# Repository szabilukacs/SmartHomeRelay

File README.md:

# SmartHome Relay 🌡️🔔

This project is a smart boiler control and monitoring system built on the **Blynk platform**. Using an **ESP32**, this system allows users to:  
- **Remotely control a relay** to activate or deactivate the built-in heating resistance of the boiler.  
- **Monitor the temperature** inside the boiler in real-time.  
- **Automate boiler heating** using thermostat-like behavior based on a set temperature range.  
- **Enable or disable notifications** for temperature changes or system events.

The project combines hardware design, embedded programming, and IoT integration for a seamless smart home experience.

---

## 📜 Table of Contents  

- [✨ Features](#features)  
- [🚀 Getting Started](#getting-started)  
  - [Hardware](#hardware)  
  - [Software](#software)  
- [⚙️ Hardware Design](#Hardware-Design)  
  - [Circuit Diagram](#circuit-diagram)  
  - [PCB 3D View](#pcb-3d-view)  
- [📲 Blynk App Interface](#blynk-app-interface)  
- [🛠️ Code Overview](#code-overview)  
  - [Dependencies](#dependencies)  
  - [Uploading the Code](#uploading-the-code)  
- [PCB Design](#pcb-design)  

## Features ✨

- **Remote Control**: Control the heating resistance via the Blynk mobile app.
- **Real-time Temperature Monitoring**: Display temperature data from the boiler directly in the app.
- **Automated Thermostat Mode**: Set a target temperature range, and the system will automatically control the relay.
- **Notification Toggle**: Enable or disable notifications for system status and alerts.
- **Custom PCB Design**: Compact and efficient PCB for the ESP32 and relay circuit, designed in KiCAD.
- **User-friendly Interface**: Intuitive and easy-to-use Blynk app interface for controlling and monitoring.

---

## Getting Started

### Hardware

- **Microcontroller**: ESP32
- **Temperature Sensor**: DS18B20  
- **Relay Module**: Controls the heating resistance
- **Custom PCB**: Designed to integrate the ESP32, relay, and sensor connections  

### Software

- **Arduino IDE**: Development environment for the ESP32 firmware  
- **Blynk**: Cloud-based platform for IoT app creation  
- **KiCAD**: Used for designing the PCB  

---

## Hardware Design📐

### Circuit Diagram

### PCB 3D View

---

## Blynk App Interface 📱

The Blynk app provides an intuitive interface for interacting with the SmartHome Relay system:

### Features:
- **Relay Control**: Toggle the relay to activate or deactivate the heating resistance.  
- **Temperature Display**: Real-time temperature monitoring from the boiler.  
- **Automation Mode**: Set a target temperature range for thermostat-like operation.  
- **Notifications Toggle**: Enable or disable notifications for system status and alerts.

---

## Code Overview

### Dependencies

Ensure the following libraries are installed in Arduino IDE:
1. **Blynk**  
2. **ESP32 Board Support**  
3. **Temperature Sensor Library**

### Uploading the Code

1. Clone the repository.
2. Open the `.ino` file in Arduino IDE.
3. Configure your WiFi and Blynk credentials in the code.
4. Upload the code to the ESP32 using a USB connection.

---

## PCB Design

- The PCB design was created using **KiCAD**.
- It includes the ESP32, relay, and connectors for the temperature sensor.
- You can [link PCB ordering instructions here] if relevant.

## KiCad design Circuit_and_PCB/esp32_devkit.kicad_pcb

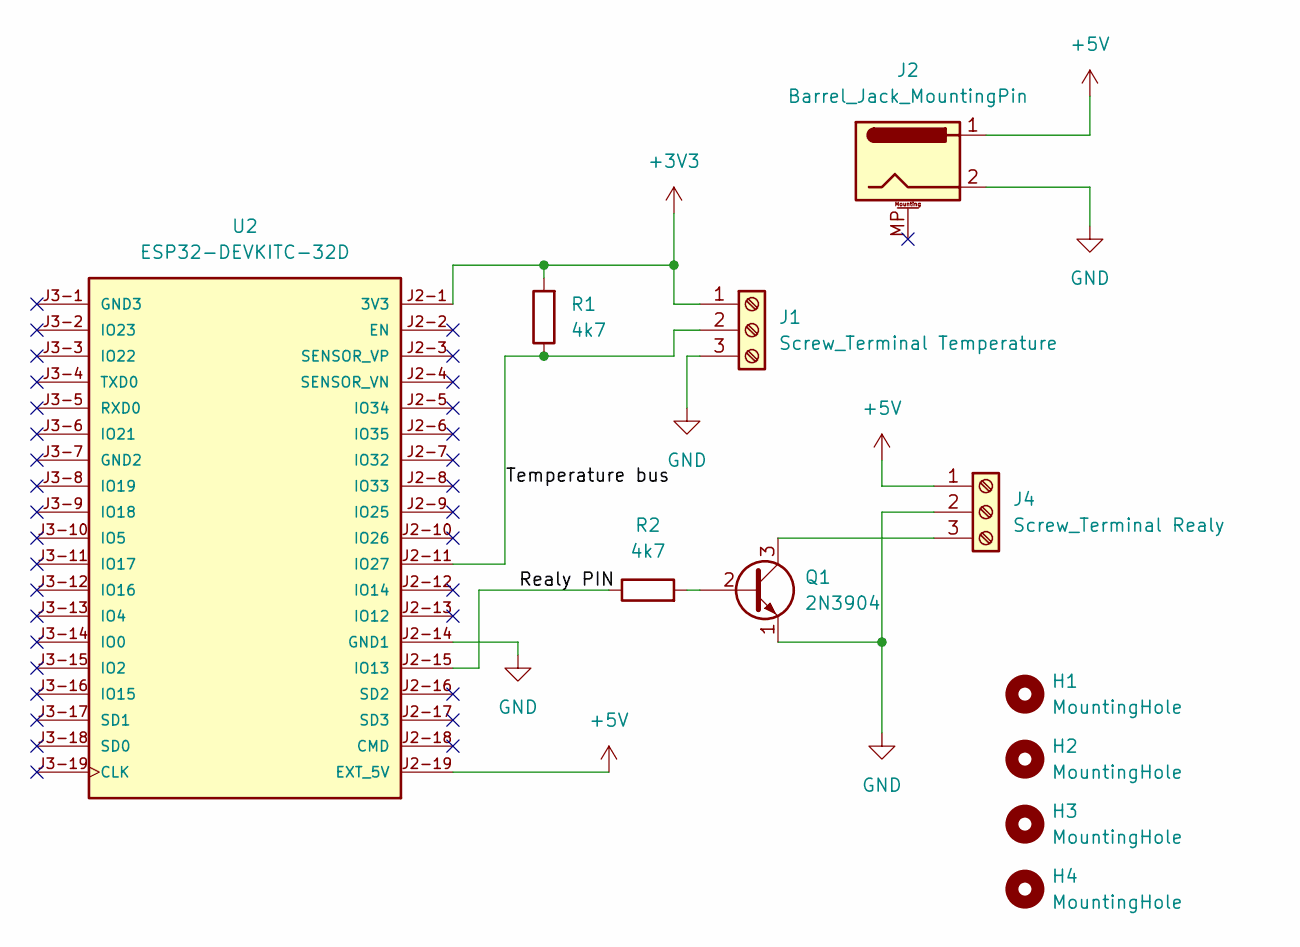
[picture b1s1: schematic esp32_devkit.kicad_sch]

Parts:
H1, H2, H3, H4: MountingHole; MountingHole_2.2mm_M2_ISO7380_Pad
J1: Screw_Terminal Temperature; TerminalBlock_bornier-3_P5.08mm
J2: Barrel_Jack_MountingPin; BarrelJack_GCT_DCJ200-10-A_Horizontal
J4: Screw_Terminal Realy; TerminalBlock_bornier-3_P5.08mm
Q1: 2N3904; TO-92_Inline_Wide
R1, R2: 4k7; R_Axial_DIN0207_L6.3mm_D2.5mm_P10.16mm_Horizontal
U2: ESP32-DEVKITC-32D; MODULE_ESP32-DEVKITC-32D; PARTREV V4

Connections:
+3V3: J1.1, R1.2, U2.J2-1 (3V3)
+5V: J2.1, J4.1, U2.J2-19 (EXT_5V)
GND: J1.3, J2.2, J4.2, Q1.1 (E), U2.J2-14 (GND1), U2.J3-7 (GND2)
unnamed: J1.2, R1.1, U2.J2-11 (IO27)
unnamed: J4.3, Q1.3 (C)
unnamed: Q1.2 (B), R2.2
unnamed: R2.1, U2.J2-15 (IO13)

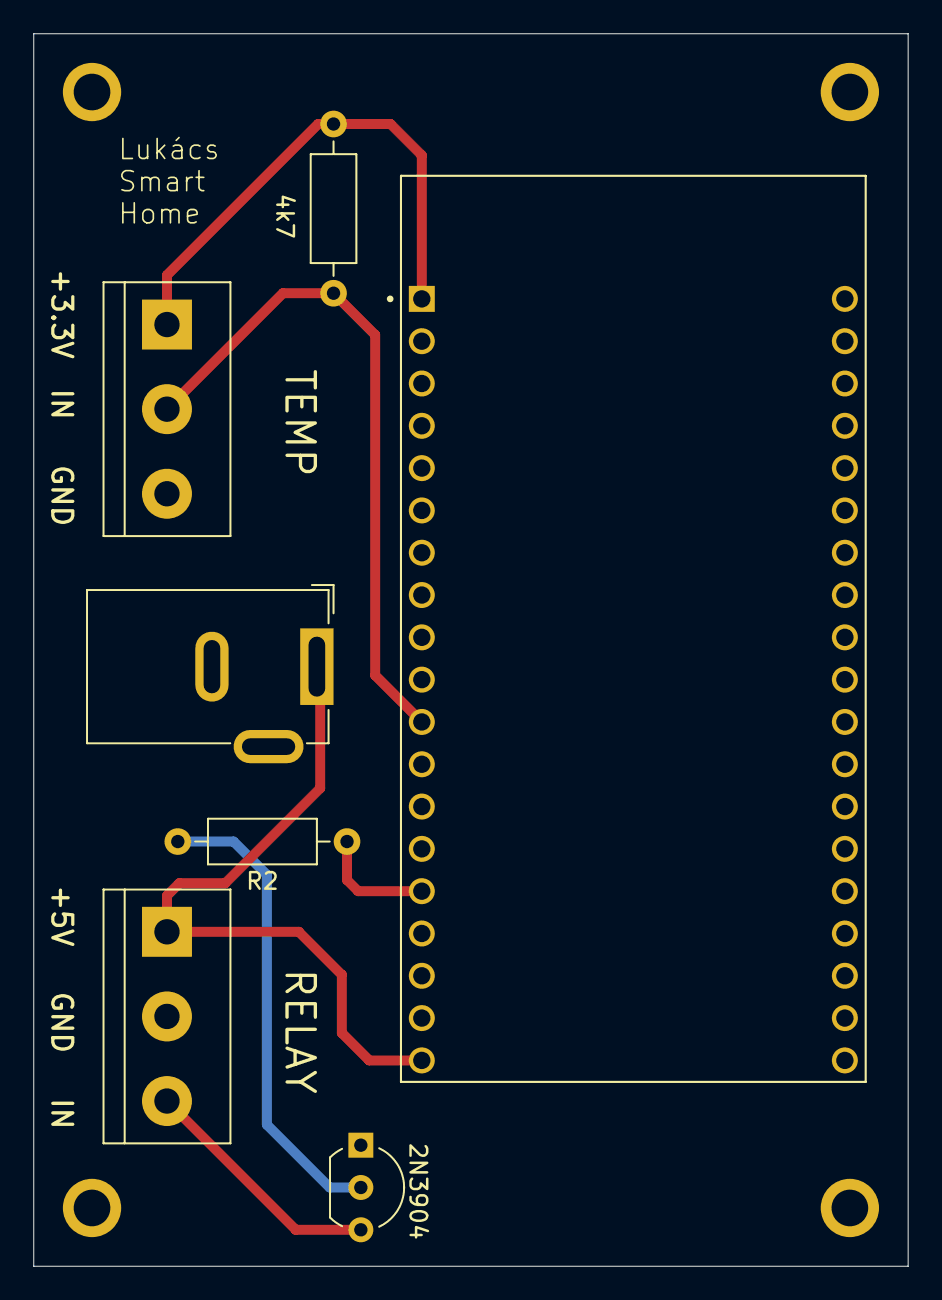
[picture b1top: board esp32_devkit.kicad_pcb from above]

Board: 2 copper layers, 52.5 x 74.0 mm, 11 parts (0 on the bottom side), 7 nets.

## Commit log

2024-11-19 Upload the project.
